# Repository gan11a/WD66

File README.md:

# WD66 ver 0.1

# As of 12/21/2023 PCB is finished, and tested.

# Witch Doctor 66 is a 65% mechanical keyboard, with layout similar to Leopold FC660M. The idea is to make it compatible with Leopold's case if you don't solder in 2 switches. I want this project to live beyond group buy (if it will ever happen), hence secondary function of PCB to be a drop-in replacement into Leopold. You can find pictures of implemented layouts and layouts planed below, as well as pictures of the PCB.
<h2>
<p align="center">
Layouts:
</p>
</h2>

<h2>
<p align="center">
PCB renders:
</p>
</h2>

<h2>
<p align="center">
Photos:
</p>
</h2>

# You are welcome to fork, modify and produce it on your own, that said I would like to be in the know about production for profit (dm me on discord: gan1a#5261); also don't be an a*s, don't erase solder mask art))). Rough to-do list is below.

# For ongoing development and planed features please refer to the [issues](https://github.com/gan11a/WD66/issues) page of WD66 Repository.

# Huge thanks to my friends FOXY and ANV3R for supporting me through this project.

# By <a href="https://11customs.com">11customs</a>

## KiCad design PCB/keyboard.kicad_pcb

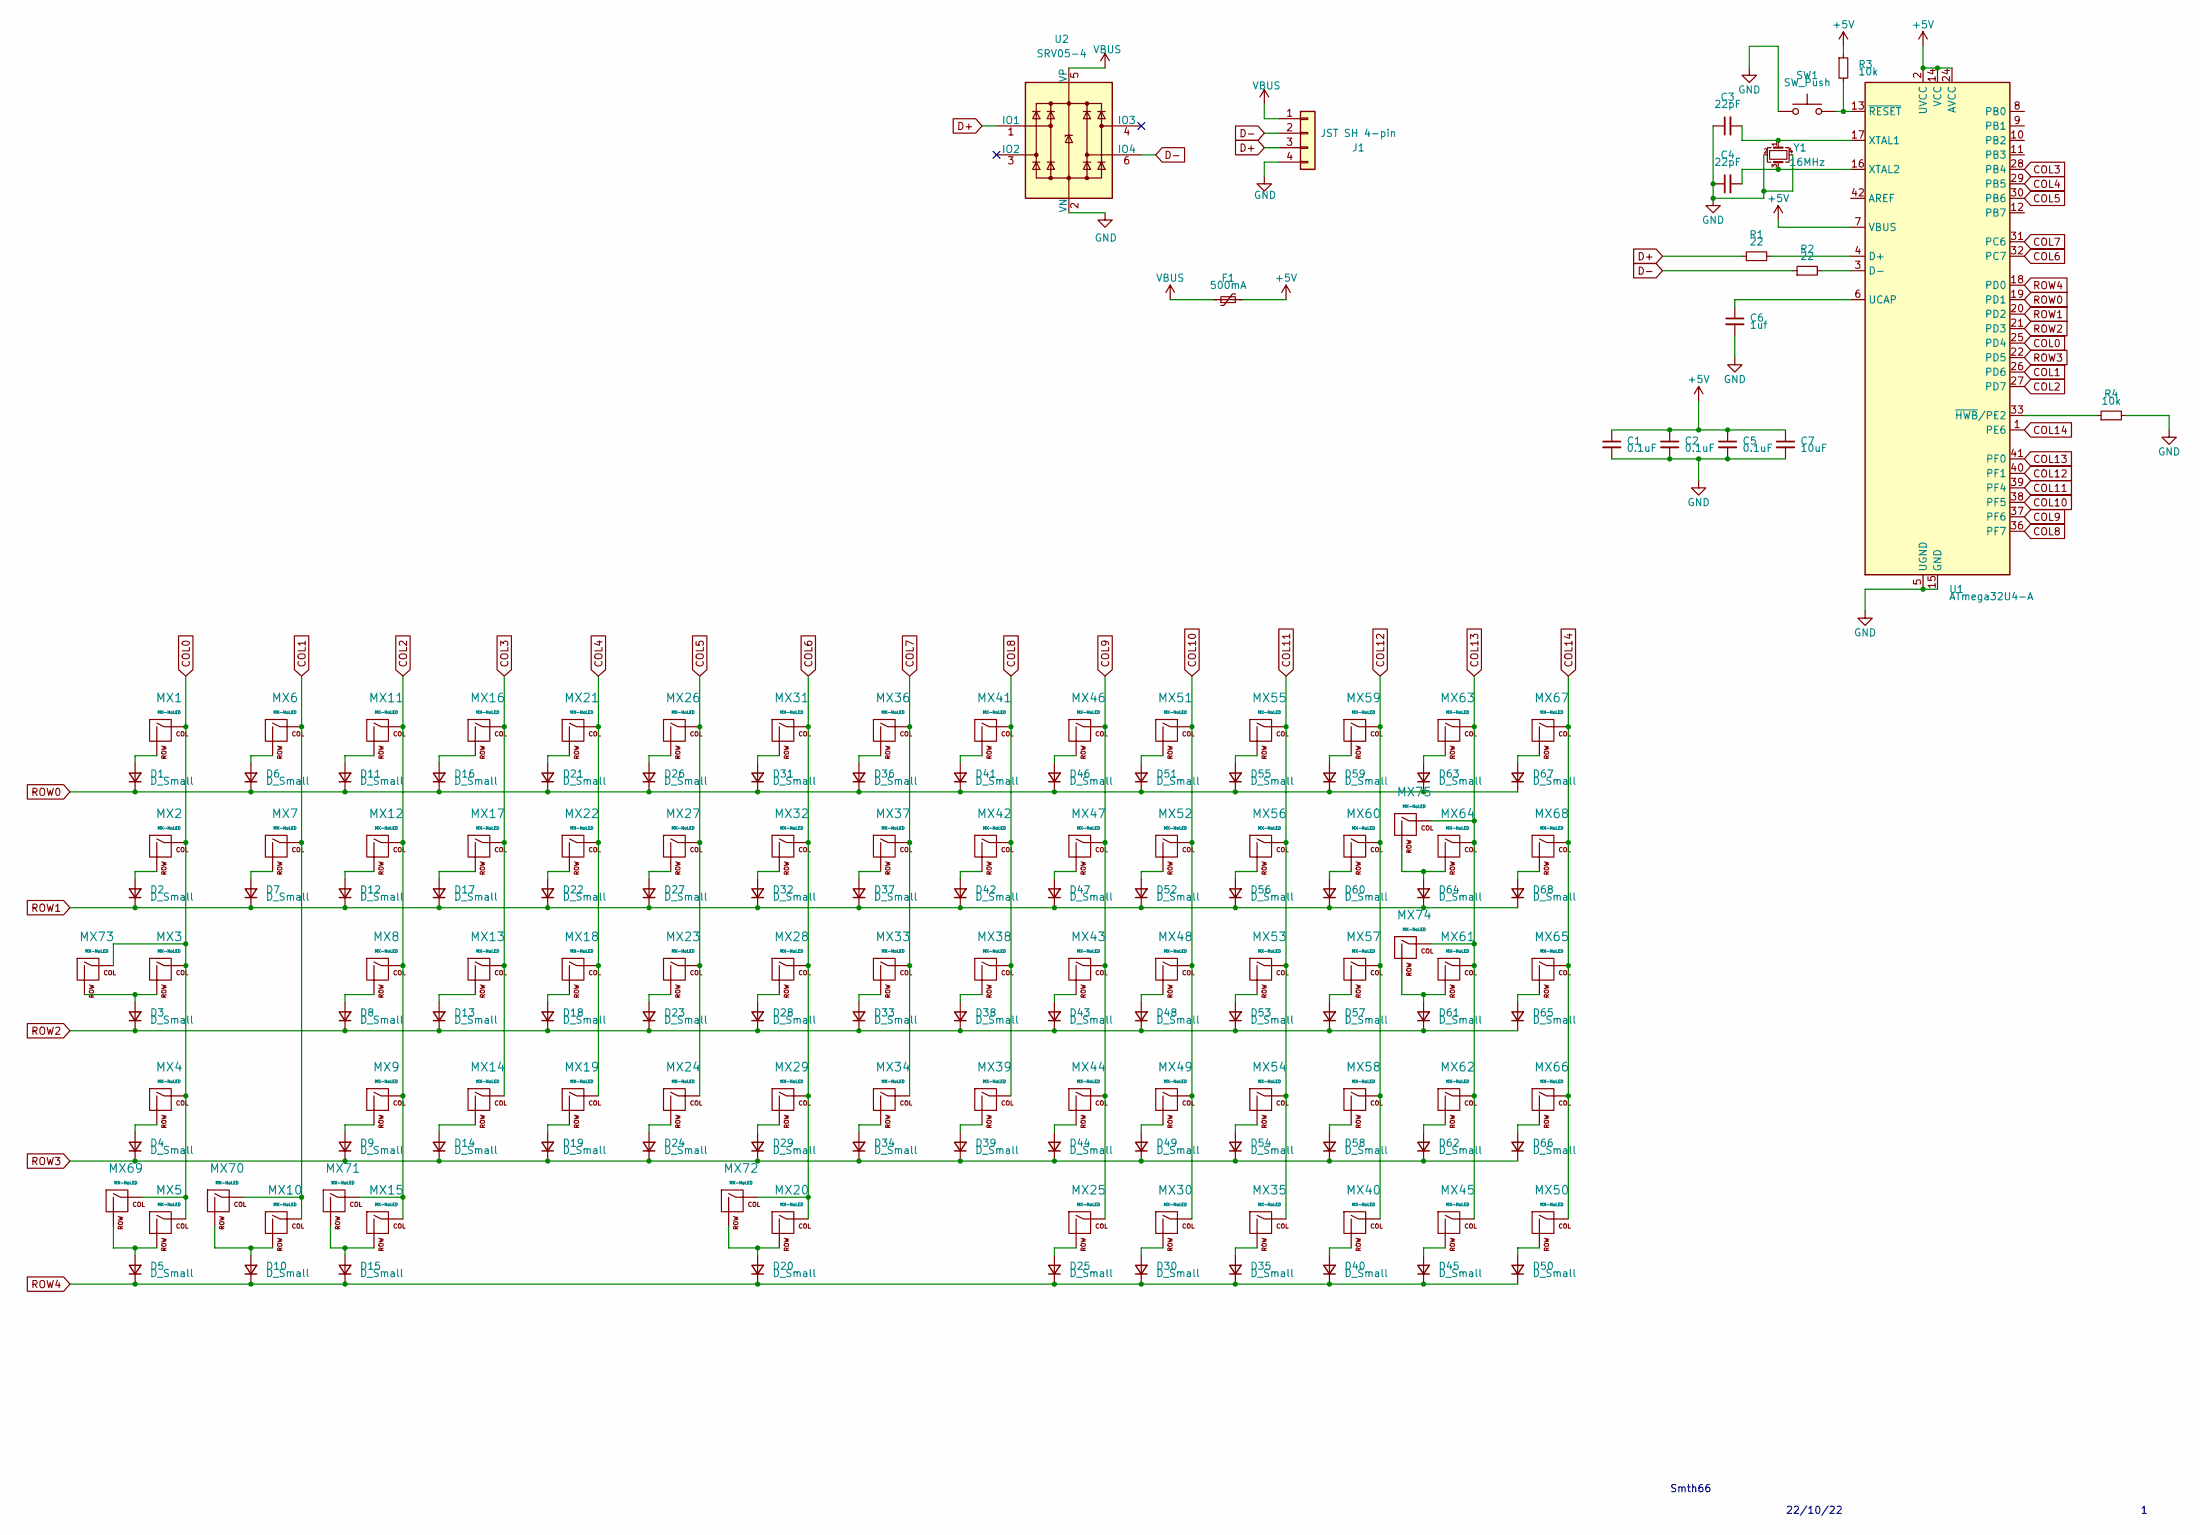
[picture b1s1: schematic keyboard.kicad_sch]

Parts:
C1, C2, C5: 0.1uF; C_0805_2012Metric
C3, C4: 22pF; C_0805_2012Metric
C6: 1uf; C_0805_2012Metric
C7: 10uF; C_0805_2012Metric
D1, D2, D3, D4, D5, D6, D7, D8, D9, D10, D11, D12, D13, D14, D15, D16, D17, D18, D19, D20, D21, D22, D23, D24, D25, D26, D27, D28, D29, D30, D31, D32, D33, D34, D35, D36, D37, D38, D39, D40, D41, D42, D43, D44, D45, D46, D47, D48, D49, D50, D51, D52, D53, D54, D55, D56, D57, D58, D59, D60, D61, D62, D63, D64, D65, D66, D67, D68: D_Small; D_SOD-123
F1: 500mA; Fuse_1206_3216Metric
J1: JST SH 4-pin; JST_SH_SM04B-SRSS-TB_1x04-1MP_P1.00mm_Horizontal; LCSC Part # C160404
MX1, MX6, MX7, MX8, MX9, MX10, MX11, MX12, MX13, MX14, MX16, MX17, MX18, MX19, MX21, MX22, MX23, MX24, MX26, MX27, MX28, MX29, MX31, MX32, MX33, MX34, MX36, MX37, MX38, MX39, MX40, MX41, MX42, MX43, MX44, MX45, MX46, MX47, MX48, MX49, MX50, MX51, MX52, MX53, MX54, MX55, MX56, MX57, MX59, MX60, MX62, MX65, MX66, MX67, MX68, MX70, MX75: MX-NoLED; MXOnly-1U-NoLED
MX2, MX64, MX69, MX71: MX-NoLED; MXOnly-1.5U-NoLED
MX3: MX-NoLED; MXOnly-1.75U-NoLED
MX4, MX58, MX61: MX-NoLED; MXOnly-2.25U-NoLED
MX5, MX15, MX25, MX30, MX35: MX-NoLED; MXOnly-1.25U-NoLED
MX20: MX-NoLED; MXOnly-6.25U-ReversedStabilizers-NoLED
MX63: MX-NoLED; MXOnly-2U-NoLED
MX72: MX-NoLED; MXOnly-7U-ReversedStabilizers-NoLED
MX73: MX-NoLED; SW_MX_1.75u_stp
MX74: MX-NoLED; MXOnly-ISO-ReversedStabilizers-NoLED
R1, R2: 22; R_0805_2012Metric
R3, R4: 10k; R_0805_2012Metric
SW1: SW_Push; SKQG-1155865
U1: ATmega32U4-A; TQFP-44_10x10mm_P0.8mm
U2: SRV05-4; SOT-23-6-routable; LCSC Part # C85364
Y1: 16MHz; Crystal_SMD_3225-4Pin_3.2x2.5mm

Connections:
+5V: C1.1, C2.1, C5.1, C7.1, F1.2, R3.1, U1.2 (UVCC), U1.7 (VBUS), U1.14 (VCC), U1.24 (AVCC), U1.34 (VCC), U1.44 (AVCC)
COL0: MX1.1 (COL), MX2.1 (COL), MX3.1 (COL), MX4.1 (COL), MX5.1 (COL), MX69.1 (COL), MX73.1 (COL), U1.25 (PD4)
COL1: MX6.1 (COL), MX7.1 (COL), MX10.1 (COL), MX70.1 (COL), U1.26 (PD6)
COL2: MX8.1 (COL), MX9.1 (COL), MX11.1 (COL), MX12.1 (COL), MX15.1 (COL), MX71.1 (COL), U1.27 (PD7)
COL3: MX13.1 (COL), MX14.1 (COL), MX16.1 (COL), MX17.1 (COL), U1.28 (PB4)
COL4: MX18.1 (COL), MX19.1 (COL), MX21.1 (COL), MX22.1 (COL), U1.29 (PB5)
COL5: MX23.1 (COL), MX24.1 (COL), MX26.1 (COL), MX27.1 (COL), U1.30 (PB6)
COL6: MX20.1 (COL), MX28.1 (COL), MX29.1 (COL), MX31.1 (COL), MX32.1 (COL), MX72.1 (COL), U1.32 (PC7)
COL7: MX33.1 (COL), MX34.1 (COL), MX36.1 (COL), MX37.1 (COL), U1.31 (PC6)
COL8: MX38.1 (COL), MX39.1 (COL), MX41.1 (COL), MX42.1 (COL), U1.36 (PF7)
COL9: MX25.1 (COL), MX43.1 (COL), MX44.1 (COL), MX46.1 (COL), MX47.1 (COL), U1.37 (PF6)
COL10: MX30.1 (COL), MX48.1 (COL), MX49.1 (COL), MX51.1 (COL), MX52.1 (COL), U1.38 (PF5)
COL11: MX35.1 (COL), MX53.1 (COL), MX54.1 (COL), MX55.1 (COL), MX56.1 (COL), U1.39 (PF4)
COL12: MX40.1 (COL), MX57.1 (COL), MX58.1 (COL), MX59.1 (COL), MX60.1 (COL), U1.40 (PF1)
COL13: MX45.1 (COL), MX61.1 (COL), MX62.1 (COL), MX63.1 (COL), MX64.1 (COL), MX74.1 (COL), MX75.1 (COL), U1.41 (PF0)
COL14: MX50.1 (COL), MX65.1 (COL), MX66.1 (COL), MX67.1 (COL), MX68.1 (COL), U1.1 (PE6)
GND: C1.2, C2.2, C3.1, C4.1, C5.2, C6.2, C7.2, J1.4, R4.2, SW1.1, U1.5 (UGND), U1.15 (GND), U1.23 (GND), U1.35 (GND), U1.43 (GND), U2.2 (VN), Y1.2, Y1.4
unnamed: D1.2 (A), MX1.2 (ROW)
unnamed: D2.2 (A), MX2.2 (ROW)
unnamed: D3.2 (A), MX3.2 (ROW), MX73.2 (ROW)
unnamed: D4.2 (A), MX4.2 (ROW)
unnamed: D5.2 (A), MX5.2 (ROW), MX69.2 (ROW)
unnamed: D6.2 (A), MX6.2 (ROW)
unnamed: D7.2 (A), MX7.2 (ROW)
unnamed: D8.2 (A), MX8.2 (ROW)
unnamed: D9.2 (A), MX9.2 (ROW)
unnamed: D10.2 (A), MX10.2 (ROW), MX70.2 (ROW)
unnamed: D11.2 (A), MX11.2 (ROW)
unnamed: D12.2 (A), MX12.2 (ROW)
unnamed: D13.2 (A), MX13.2 (ROW)
unnamed: D14.2 (A), MX14.2 (ROW)
unnamed: D15.2 (A), MX15.2 (ROW), MX71.2 (ROW)
unnamed: D16.2 (A), MX16.2 (ROW)
unnamed: D17.2 (A), MX17.2 (ROW)
unnamed: D18.2 (A), MX18.2 (ROW)
unnamed: D19.2 (A), MX19.2 (ROW)
unnamed: D20.2 (A), MX20.2 (ROW), MX72.2 (ROW)
unnamed: D21.2 (A), MX21.2 (ROW)
unnamed: D22.2 (A), MX22.2 (ROW)
unnamed: D23.2 (A), MX23.2 (ROW)
unnamed: D24.2 (A), MX24.2 (ROW)
unnamed: D25.2 (A), MX25.2 (ROW)
unnamed: D26.2 (A), MX26.2 (ROW)
unnamed: D27.2 (A), MX27.2 (ROW)
unnamed: D28.2 (A), MX28.2 (ROW)
unnamed: D29.2 (A), MX29.2 (ROW)
unnamed: D30.2 (A), MX30.2 (ROW)
unnamed: D31.2 (A), MX31.2 (ROW)
unnamed: D32.2 (A), MX32.2 (ROW)
unnamed: D33.2 (A), MX33.2 (ROW)
unnamed: D34.2 (A), MX34.2 (ROW)
unnamed: D35.2 (A), MX35.2 (ROW)
unnamed: D36.2 (A), MX36.2 (ROW)
unnamed: D37.2 (A), MX37.2 (ROW)
unnamed: D38.2 (A), MX38.2 (ROW)
unnamed: D39.2 (A), MX39.2 (ROW)
unnamed: D40.2 (A), MX40.2 (ROW)
unnamed: D41.2 (A), MX41.2 (ROW)
unnamed: D42.2 (A), MX42.2 (ROW)
unnamed: D43.2 (A), MX43.2 (ROW)
unnamed: D44.2 (A), MX44.2 (ROW)
unnamed: D45.2 (A), MX45.2 (ROW)
unnamed: D46.2 (A), MX46.2 (ROW)
unnamed: D47.2 (A), MX47.2 (ROW)
unnamed: D48.2 (A), MX48.2 (ROW)
unnamed: D49.2 (A), MX49.2 (ROW)
unnamed: D50.2 (A), MX50.2 (ROW)
unnamed: D51.2 (A), MX51.2 (ROW)
unnamed: D52.2 (A), MX52.2 (ROW)
unnamed: D53.2 (A), MX53.2 (ROW)
unnamed: D54.2 (A), MX54.2 (ROW)
unnamed: D55.2 (A), MX55.2 (ROW)
unnamed: D56.2 (A), MX56.2 (ROW)
unnamed: D57.2 (A), MX57.2 (ROW)
unnamed: D58.2 (A), MX58.2 (ROW)
unnamed: D59.2 (A), MX59.2 (ROW)
unnamed: D60.2 (A), MX60.2 (ROW)
unnamed: D61.2 (A), MX61.2 (ROW), MX74.2 (ROW)
unnamed: D62.2 (A), MX62.2 (ROW)
unnamed: D63.2 (A), MX63.2 (ROW)
unnamed: D64.2 (A), MX64.2 (ROW), MX75.2 (ROW)
unnamed: D65.2 (A), MX65.2 (ROW)
unnamed: D66.2 (A), MX66.2 (ROW)
unnamed: D67.2 (A), MX67.2 (ROW)
unnamed: D68.2 (A), MX68.2 (ROW)
unnamed: C6.1, U1.6 (UCAP)
unnamed: C3.2, U1.17 (XTAL1), Y1.1
unnamed: C4.2, U1.16 (XTAL2), Y1.3
unnamed: R4.1, U1.33 (~HWB/PE2)
unnamed: R3.2, SW1.2, U1.13 (~RESET)
ROW0: D1.1 (K), D6.1 (K), D11.1 (K), D16.1 (K), D21.1 (K), D26.1 (K), D31.1 (K), D36.1 (K), D41.1 (K), D46.1 (K), D51.1 (K), D55.1 (K), D59.1 (K), D63.1 (K), D67.1 (K), U1.19 (PD1)
ROW1: D2.1 (K), D7.1 (K), D12.1 (K), D17.1 (K), D22.1 (K), D27.1 (K), D32.1 (K), D37.1 (K), D42.1 (K), D47.1 (K), D52.1 (K), D56.1 (K), D60.1 (K), D64.1 (K), D68.1 (K), U1.20 (PD2)
ROW2: D3.1 (K), D8.1 (K), D13.1 (K), D18.1 (K), D23.1 (K), D28.1 (K), D33.1 (K), D38.1 (K), D43.1 (K), D48.1 (K), D53.1 (K), D57.1 (K), D61.1 (K), D65.1 (K), U1.21 (PD3)
ROW3: D4.1 (K), D9.1 (K), D14.1 (K), D19.1 (K), D24.1 (K), D29.1 (K), D34.1 (K), D39.1 (K), D44.1 (K), D49.1 (K), D54.1 (K), D58.1 (K), D62.1 (K), D66.1 (K), U1.22 (PD5)
ROW4: D5.1 (K), D10.1 (K), D15.1 (K), D20.1 (K), D25.1 (K), D30.1 (K), D35.1 (K), D40.1 (K), D45.1 (K), D50.1 (K), U1.18 (PD0)
VBUS: F1.1, J1.1, U2.5 (VP)

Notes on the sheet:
Smth66
22/10/22

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
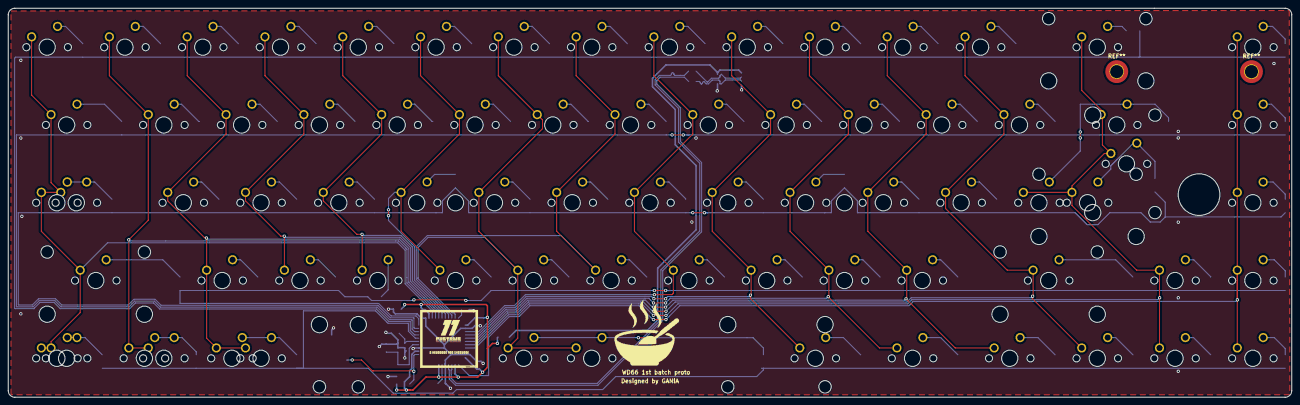
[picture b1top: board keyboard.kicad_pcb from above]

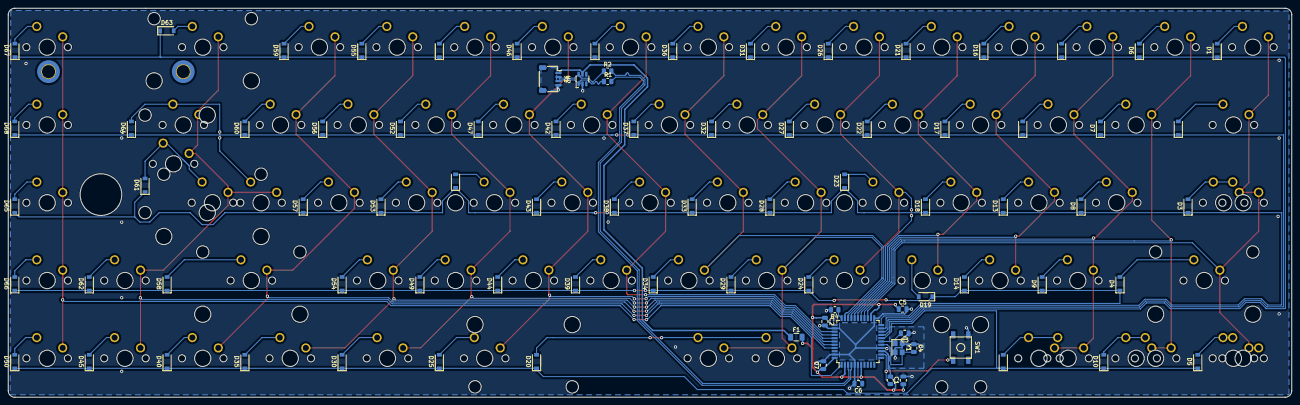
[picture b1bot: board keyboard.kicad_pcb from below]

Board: 2 copper layers, 314.3 x 95.3 mm, 160 parts (85 on the bottom side), 98 nets.

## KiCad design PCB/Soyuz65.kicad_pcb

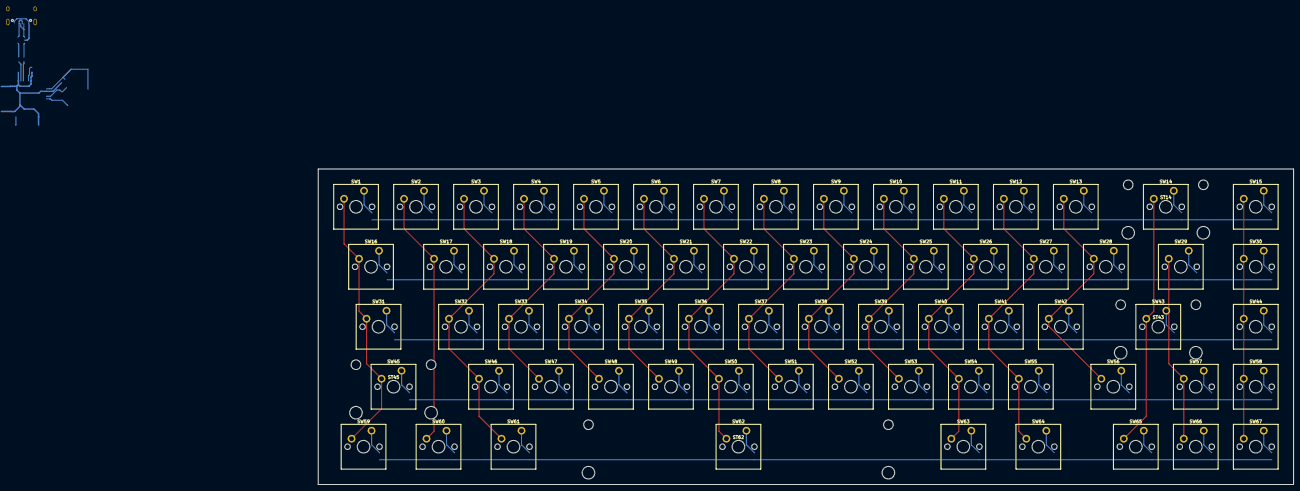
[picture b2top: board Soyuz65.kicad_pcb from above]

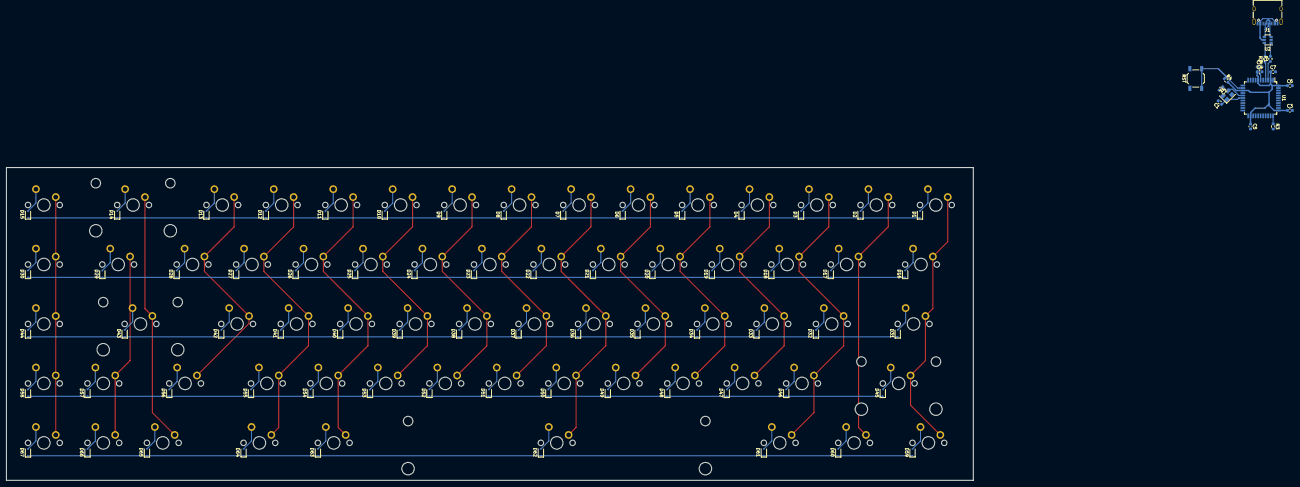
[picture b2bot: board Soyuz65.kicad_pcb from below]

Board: 2 copper layers, 309.8 x 100.2 mm, 155 parts (84 on the bottom side), 101 nets.

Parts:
C1, C2: 22p; C_0603_1608Metric
C3, C4, C5, C6: 0.1u; C_0603_1608Metric
C7: 4.7u; C_0603_1608Metric
C8: 1u; C_0603_1608Metric
D1, D2, D3, D4, D5, D6, D7, D8, D9, D10, D11, D12, D13, D14, D15, D16, D17, D18, D19, D20, D21, D22, D23, D24, D25, D26, D27, D28, D29, D30, D31, D32, D33, D34, D35, D36, D37, D38, D39, D40, D41, D42, D43, D44, D45, D46, D47, D48, D49, D50, D51, D52, D53, D54, D55, D56, D57, D58, D59, D60, D61, D62, D63, D64, D65, D66, D67: D; D_SOD-323F
J1: USB_C_Receptacle_USB2.0; USB_C_Receptacle_XKB_U262-16XN-4BVC11
R1, R2: 22; R_0603_1608Metric
R3, R4: 10k; R_0603_1608Metric
RST: SW_SPST; SW_SPST_TL3342
ST14, ST43, ST45: MountingHole; Stabilizer_Cherry_MX_2u
ST62: MountingHole; Stabilizer_Cherry_MX_6u
SW1, SW2, SW3, SW4, SW5, SW6, SW7, SW8, SW9, SW10, SW11, SW12, SW13, SW15, SW17, SW18, SW19, SW20, SW21, SW22, SW23, SW24, SW25, SW26, SW27, SW28, SW30, SW32, SW33, SW34, SW35, SW36, SW37, SW38, SW39, SW40, SW41, SW42, SW44, SW46, SW47, SW48, SW49, SW50, SW51, SW52, SW53, SW54, SW55, SW57, SW58, SW65, SW66, SW67: SW_Push; SW_Cherry_MX_PCB_1.00u
SW14: SW_Push; SW_Cherry_MX_PCB_2.00u
SW16, SW29: SW_Push; SW_Cherry_MX_PCB_1.50u
SW31, SW56: SW_Push; SW_Cherry_MX_PCB_1.75u
SW43, SW45: SW_Push; SW_Cherry_MX_PCB_2.25u
SW59, SW60, SW61, SW63, SW64: SW_Push; SW_Cherry_MX_PCB_1.25u
SW62: SW_Push; SW_Cherry_MX_PCB_6.25u
U1: ATmega16U4-AU; TQFP-44_10x10mm_P0.8mm
U2: TPD2S017; SOT-23-6
Y1: Crystal_GND24; Crystal_SMD_3225-4Pin_3.2x2.5mm

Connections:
COL5: SW1.1, SW16.1, SW31.1, SW45.1, SW59.1, U1.29
COL6: SW2.1, SW17.1, SW60.1, U1.30
COL7: SW3.1, SW18.1, SW32.1, SW46.1, SW61.1, U1.12
COL8: SW4.1, SW19.1, SW33.1, SW47.1, U1.31
COL9: SW5.1, SW20.1, SW34.1, SW48.1, U1.32
COL10: SW6.1, SW21.1, SW35.1, SW49.1, U1.18
COL11: SW7.1, SW22.1, SW36.1, SW50.1, SW62.1, U1.19
COL12: SW8.1, SW23.1, SW37.1, SW51.1, U1.20
COL13: SW9.1, SW24.1, SW38.1, SW52.1, U1.21
COL14: SW10.1, SW25.1, SW39.1, SW53.1, U1.25
COL15: SW11.1, SW26.1, SW40.1, SW54.1, SW63.1, U1.22
COL16: SW12.1, SW27.1, SW41.1, SW55.1, SW64.1, U1.26
COL17: SW13.1, SW28.1, SW42.1, SW56.1, U1.27
COL18: SW14.1, SW43.1, SW65.1, U1.41
COL19: SW29.1, SW57.1, SW66.1, U1.39
COL20: SW15.1, SW30.1, SW44.1, SW58.1, SW67.1, U1.40
GND: C1.2, C2.2, C3.2, C4.2, C5.2, C6.2, C7.2, C8.2, J1.A1, J1.A12, J1.B1, J1.B12, J1.S1, R3.2, RST.1, U1.5, U1.15, U1.23, U1.35, U1.43, U2.2, Y1.2, Y1.4
unnamed: D1.2, SW1.2
unnamed: D2.2, SW2.2
unnamed: D3.2, SW3.2
unnamed: D4.2, SW4.2
unnamed: D5.2, SW5.2
unnamed: D6.2, SW6.2
unnamed: D7.2, SW7.2
unnamed: D8.2, SW8.2
unnamed: D9.2, SW9.2
unnamed: D10.2, SW10.2
unnamed: D11.2, SW11.2
unnamed: D12.2, SW12.2
unnamed: D13.2, SW13.2
unnamed: D14.2, SW14.2
unnamed: D15.2, SW15.2
unnamed: D16.2, SW16.2
unnamed: D17.2, SW17.2
unnamed: D18.2, SW18.2
unnamed: D19.2, SW19.2
unnamed: D20.2, SW20.2
unnamed: D21.2, SW21.2
unnamed: D22.2, SW22.2
unnamed: D23.2, SW23.2
unnamed: D24.2, SW24.2
unnamed: D25.2, SW25.2
unnamed: D26.2, SW26.2
unnamed: D27.2, SW27.2
unnamed: D28.2, SW28.2
unnamed: D29.2, SW29.2
unnamed: D30.2, SW30.2
unnamed: D31.2, SW31.2
unnamed: D32.2, SW32.2
unnamed: D33.2, SW33.2
unnamed: D34.2, SW34.2
unnamed: D35.2, SW35.2
unnamed: D36.2, SW36.2
unnamed: D37.2, SW37.2
unnamed: D38.2, SW38.2
unnamed: D39.2, SW39.2
unnamed: D40.2, SW40.2
unnamed: D41.2, SW41.2
unnamed: D42.2, SW42.2
unnamed: D43.2, SW43.2
unnamed: D44.2, SW44.2
unnamed: D45.2, SW45.2
unnamed: D46.2, SW46.2
unnamed: D47.2, SW47.2
unnamed: D48.2, SW48.2
unnamed: D49.2, SW49.2
unnamed: D50.2, SW50.2
unnamed: D51.2, SW51.2
unnamed: D52.2, SW52.2
unnamed: D53.2, SW53.2
unnamed: D54.2, SW54.2
unnamed: D55.2, SW55.2
unnamed: D56.2, SW56.2
unnamed: D57.2, SW57.2
unnamed: D58.2, SW58.2
unnamed: D59.2, SW59.2
unnamed: D60.2, SW60.2
unnamed: D61.2, SW61.2
unnamed: D62.2, SW62.2
unnamed: D63.2, SW63.2
unnamed: D64.2, SW64.2
unnamed: D65.2, SW65.2
unnamed: D66.2, SW66.2
unnamed: D67.2, SW67.2
ROW0: D1.1, D2.1, D3.1, D4.1, D5.1, D6.1, D7.1, D8.1, D9.1, D10.1, D11.1, D12.1, D13.1, D14.1, D15.1, U1.8
ROW1: D16.1, D17.1, D18.1, D19.1, D20.1, D21.1, D22.1, D23.1, D24.1, D25.1, D26.1, D27.1, D28.1, D29.1, D30.1, U1.9
ROW2: D31.1, D32.1, D33.1, D34.1, D35.1, D36.1, D37.1, D38.1, D39.1, D40.1, D41.1, D42.1, D43.1, D44.1, U1.10
ROW3: D45.1, D46.1, D47.1, D48.1, D49.1, D50.1, D51.1, D52.1, D53.1, D54.1, D55.1, D56.1, D57.1, D58.1, U1.11
ROW4: D59.1, D60.1, D61.1, D62.1, D63.1, D64.1, D65.1, D66.1, D67.1, U1.28
VCC: C3.1, C4.1, C5.1, C6.1, C7.1, J1.A4, J1.A9, J1.B4, J1.B9, R4.2, U1.2, U1.14, U1.24, U1.34, U1.44, U2.5
mcu/D+: R2.1, U1.4
mcu/D-: R1.1, U1.3
mcu/UCAP: C8.1, U1.6
mcu/XTAL1: C1.1, U1.17, Y1.1
mcu/XTAL2: C2.1, U1.16, Y1.3
mcu/~HWB/PE2: R3.1, U1.33
mcu/~RESET: R4.1, RST.2, U1.13
u2/D+: R2.2, U2.6
u2/D-: R1.2, U2.1
usb/D+: J1.A6, J1.B6, U2.4
usb/D-: J1.A7, J1.B7, U2.3

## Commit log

2022-10-21 small updates
2022-10-22 Added submodules
2022-10-22 Changed PCB Design
2022-10-22 fixed pcb folder
2022-10-22 configured footprints
2022-10-22 eddited README.md
2022-10-22 created MCU schematic
2022-10-23 added USB and Switch to schematic
2022-10-23 added switch grid to schematic
2022-10-24 Updated name
2022-11-02 Finnished Schematic????
2022-11-04 smth wierd wan't commited lol
2022-11-04 Started pcb development
2022-11-04 still working on pcb
2022-11-05 some backup files
2022-11-05 fixed footprints
2022-11-05 PCB work in progress
2022-11-06 mocked up pcb
2022-11-08 updated schematic to work with unified daughterboard
2022-11-10 changed pcb to work with unified daughterboard
2022-11-20 Working on traces
2022-11-21 finnished traces
2022-11-26 Finished PCB designed, still not tested
2022-11-26 updated 2
2022-12-06 added holes for center standoffs
2022-12-06 edited readme
2022-12-06 updated silkscreen
2022-12-26 add beta branch
2022-12-27 started redoing wiring
2022-12-27 updated README.md for beta branch
2022-12-27 all new pretty wiring
2022-12-29 added a hole
2023-01-04 started rewiring
2023-01-07 smoothed out the wiring
2023-01-09 Redid wiring again
2023-01-09 Differential pair done
2023-01-16 started reworking wiring (again), only mx footprints now
2023-01-16 redid wiring (again) no checks yet
2023-01-17 still working on wiring
2023-01-19 finnished implementing layouts
2023-01-23 relocated JST
2023-01-28 trying production
2023-02-12 final touch ups
2023-04-14 misc updated
2023-12-21 production files and last small changes to v0.1
2024-01-21 changed README.md
2024-01-26 added photos to readme.md
2024-01-26 started fixing daughterboard mount
2024-01-27 Added firmware
2024-01-27 Updated firmware, hex not updated
2024-01-27 working on firmware
2024-01-30 final version of rev0.1 firmware
2024-09-08 changes to v1.5 pcb
2024-09-08 added mounting for new uDB
